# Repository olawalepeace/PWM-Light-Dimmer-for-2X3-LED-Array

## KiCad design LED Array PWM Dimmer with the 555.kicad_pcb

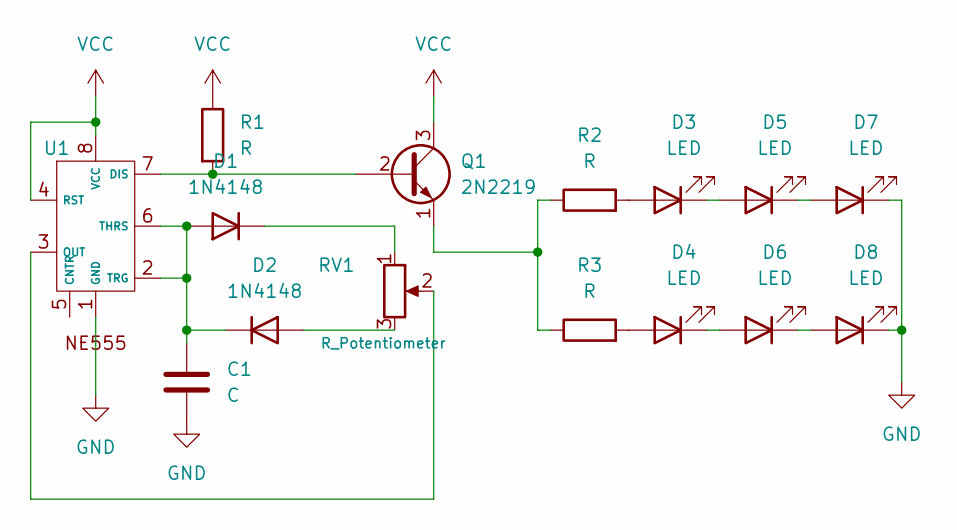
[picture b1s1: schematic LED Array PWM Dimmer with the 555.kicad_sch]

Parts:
C1: C; C_Radial_D6.3mm_H11.0mm_P2.50mm
D1, D2: 1N4148; D_DO-35_SOD27_P7.62mm_Horizontal
D3, D4, D5, D6, D7, D8: LED; LED_D3.0mm
Q1: 2N2219; TO-39-3
R1, R2, R3: R; R_Axial_DIN0207_L6.3mm_D2.5mm_P10.16mm_Horizontal
RV1: R_Potentiometer; Potentiometer_Alps_RK163_Single_Horizontal
U1: ICM7555-PDIP

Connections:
GND: C1.2, D7.1 (K), D8.1 (K), U1.1 (GND)
unnamed: C1.1, D1.2 (A), D2.1 (K), U1.2 (TRG), U1.6 (THRS)
unnamed: D1.1 (K), RV1.1
unnamed: D2.2 (A), RV1.3
unnamed: D3.2 (A), R2.2
unnamed: D3.1 (K), D5.2 (A)
unnamed: D4.2 (A), R3.2
unnamed: D4.1 (K), D6.2 (A)
unnamed: D5.1 (K), D7.2 (A)
unnamed: D6.1 (K), D8.2 (A)
unnamed: Q1.2 (B), R1.2, U1.7 (DIS)
unnamed: Q1.1 (E), R2.1, R3.1
unnamed: RV1.2, U1.3 (OUT)
VCC: Q1.3 (C), R1.1, U1.4 (RST), U1.8 (VCC)

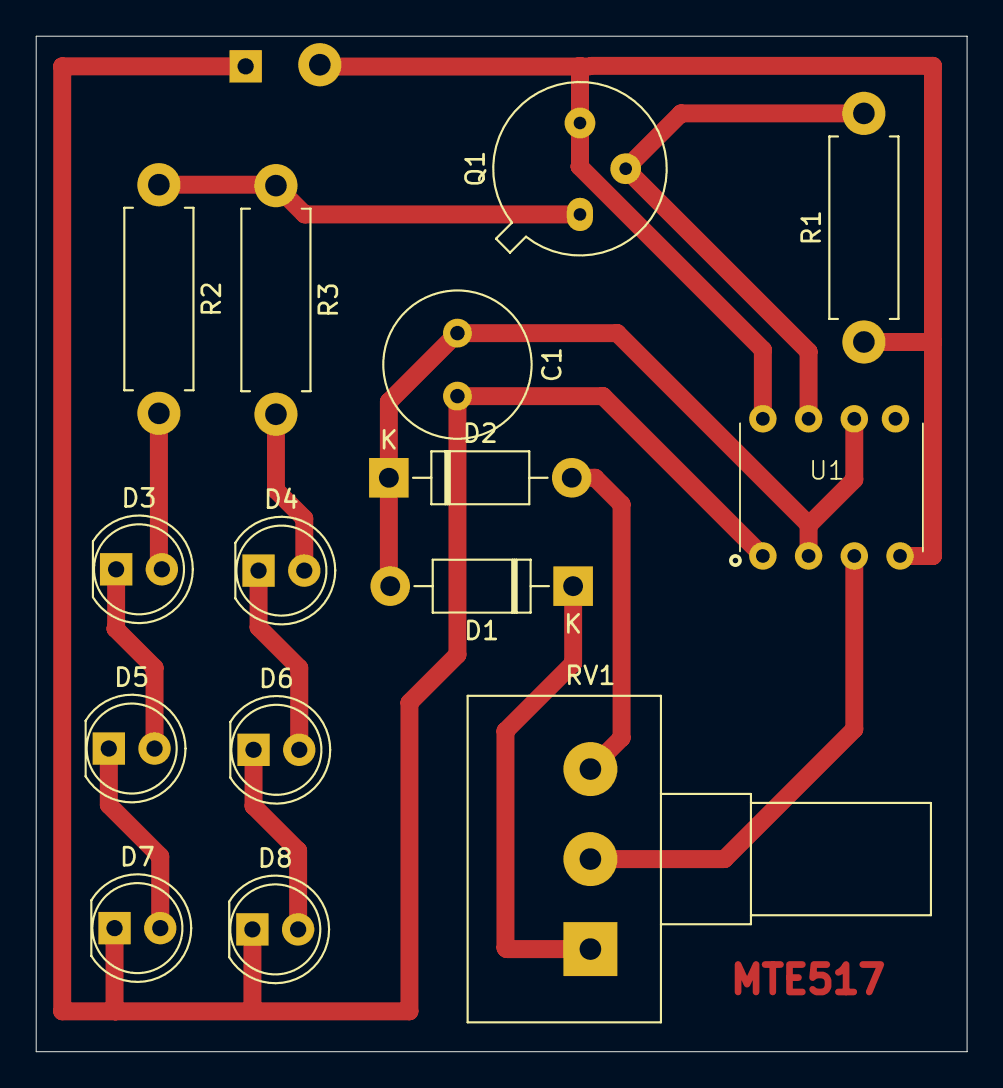
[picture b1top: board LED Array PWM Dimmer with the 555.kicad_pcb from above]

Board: 2 copper layers, 51.7 x 56.4 mm, 15 parts (0 on the bottom side), 14 nets.
